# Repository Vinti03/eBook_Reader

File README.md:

# OpenBook E-Book Reader
Made by: Vintilescu Andrei-Florin, 332CA

University: UNSTPB, Bucharest

## Conținutul Repository-ului

OpenBook

    Hardware

        OpenBook.sch            // Fișierul schematic

        OpenBook.brd            // Fișierul PCB

    Manufacturing

        gerbers.zip             // Pachetul Gerber generat

        OpenBook.bom            // Bill Of Materials (BOM)

        OpenBook.cpl            // Fișier Pick and Place

    Mechanical

        OpenBook_exploded.step  // Model 3D exploded view (PCB + baterie + display + carcasă)

        OpenBook_Fusion360.f3d  // Fișierul 3D nativ Fusion360

    Images

        pcb_render.png          // Imagine cu randări ale PCB-ului

        device_render.png       // Randări ale dispozitivului complet

    LICENSE                     // Licența open source (ex. Apache 2.0)

    README.md                   // Acest fișier

## Diagramă Bloc a Sistemului

## Bill Of Materials (BOM)

| Device                                                                                  | DATASHEET                                                                                                     | PURCHASE-URL                                                                                                                            |
|-----------------------------------------------------------------------------------------|---------------------------------------------------------------------------------------------------------------|-----------------------------------------------------------------------------------------------------------------------------------------|
| ADAFRUIT_LEDCHIP-LED0603                                                                | https://www.snapeda.com/parts/KP-1608SURCK/Kingbright/datasheet/                                              | https://www.snapeda.com/parts/KP-1608SURCK/Kingbright/view-part/?ref=search&t=LED%200603                                                  |
| ESP32_WROVER_EAGLE-LTSPICE_RR0402                                                       | https://analytics.supplyframe.com/trackingservlet/track/?r=0x34... (link lung)                                | https://componentsearchengine.com/part-view/R0402%201%25%20100%20K%20(RC0402FR-07100KL)/YAGEO                                          |
| SJ                                                                                      | https://grabcad.com/library/solder-jumpers-1                                                                  | https://grabcad.com/library/solder-jumpers-1                                                                                            |
| EAGLE-LTSPICE_CC0402                                                                    | https://analytics.supplyframe.com/trackingservlet/track/?r=0x34... (link lung)                                | https://componentsearchengine.com/part-view/CC0402MRX5R5BB106/YAGEO                                                                    |
| ESP32_WROVER_EAGLE-LTSPICE_RR0402                                                       | https://analytics.supplyframe.com/trackingservlet/track/?r=0x34... (link lung)                                | https://componentsearchengine.com/part-view/R0402%201%25%20100%20K%20(RC0402FR-07100KL)/YAGEO                                          |
| ESP32_WROVER_EAGLE-LTSPICE_RR0402                                                       | https://analytics.supplyframe.com/trackingservlet/track/?r=0x34... (link lung)                                | https://componentsearchengine.com/part-view/R0402%201%25%20100%20K%20(RC0402FR-07100KL)/YAGEO                                          |
| EAGLE-LTSPICE_CC0402                                                                    | https://analytics.supplyframe.com/trackingservlet/track/?r=0x34... (link lung)                                | https://componentsearchengine.com/part-view/CC0402MRX5R5BB106/YAGEO                                                                    |
| RCL_CPOL-EUCT3528                                                                       | https://s3.amazonaws.com/snapeda/datasheet/TAJB475K025RNJ_AVX.pdf                                             | https://www.snapeda.com/parts/TAJB475K025RNJ/AVX/view-part/?ref=dk&t=capacitor%203528&con_ref=None                                     |
| ESP32_WROVER_EAGLE-LTSPICE_RR0402                                                       | https://analytics.supplyframe.com/trackingservlet/track/?r=0x34... (link lung)                                | https://componentsearchengine.com/part-view/R0402%201%25%20100%20K%20(RC0402FR-07100KL)/YAGEO                                          |
| ESP32_WROVER_EAGLE-LTSPICE_RR0402                                                       | https://analytics.supplyframe.com/trackingservlet/track/?r=0x34... (link lung)                                | https://componentsearchengine.com/part-view/R0402%201%25%20100%20K%20(RC0402FR-07100KL)/YAGEO                                          |
| EAGLE-LTSPICE_CC0402                                                                    | https://analytics.supplyframe.com/trackingservlet/track/?r=0x34... (link lung)                                | https://componentsearchengine.com/part-view/CC0402MRX5R5BB106/YAGEO                                                                    |
| 112A-TAAR-R03_ATTEND                                                                    | https://store.comet.srl.ro/Catalogue/Product/43497/                                                           | https://store.comet.srl.ro/Catalogue/Product/43497/                                                                                     |
| ESP32_WROVER_EAGLE-LTSPICE_RR0402                                                       | https://analytics.supplyframe.com/trackingservlet/track/?r=0x34... (link lung)                                | https://componentsearchengine.com/part-view/R0402%201%25%20100%20K%20(RC0402FR-07100KL)/YAGEO                                          |
| EAGLE-LTSPICE_CC0402                                                                    | https://analytics.supplyframe.com/trackingservlet/track/?r=0x34... (link lung)                                | https://componentsearchengine.com/part-view/CC0402MRX5R5BB106/YAGEO                                                                    |
| EAGLE-LTSPICE_CC0402                                                                    | https://analytics.supplyframe.com/trackingservlet/track/?r=0x34... (link lung)                                | https://componentsearchengine.com/part-view/CC0402MRX5R5BB106/YAGEO                                                                    |
| ESP32_WROVER_EAGLE-LTSPICE_RR0402                                                       | https://analytics.supplyframe.com/trackingservlet/track/?r=0x34... (link lung)                                | https://componentsearchengine.com/part-view/R0402%201%25%20100%20K%20(RC0402FR-07100KL)/YAGEO                                          |
| ESP32_WROVER_EAGLE-LTSPICE_RR0402                                                       | https://analytics.supplyframe.com/trackingservlet/track/?r=0x34... (link lung)                                | https://componentsearchengine.com/part-view/R0402%201%25%20100%20K%20(RC0402FR-07100KL)/YAGEO                                          |
| ESP32_WROVER_SPARKFUN-DISCRETESEMI_MOSFET_PCH-DMG2305UX-7                               | https://analytics.supplyframe.com/trackingservlet/track/?r=0x34... (link lung)                                | https://componentsearchengine.com/part-view/DMG2305UX-7/Diodes%20Incorporated                                                         |
| ESP32_WROVER_EAGLE-LTSPICE_RR0402                                                       | https://analytics.supplyframe.com/trackingservlet/track/?r=0x34... (link lung)                                | https://componentsearchengine.com/part-view/R0402%201%25%20100%20K%20(RC0402FR-07100KL)/YAGEO                                          |
| EAGLE-LTSPICE_CC0402                                                                    | https://analytics.supplyframe.com/trackingservlet/track/?r=0x34... (link lung)                                | https://componentsearchengine.com/part-view/CC0402MRX5R5BB106/YAGEO                                                                    |
| EAGLE-LTSPICE_CC0402                                                                    | https://analytics.supplyframe.com/trackingservlet/track/?r=0x34... (link lung)                                | https://componentsearchengine.com/part-view/CC0402MRX5R5BB106/YAGEO                                                                    |
| ESP32_WROVER_EAGLE-LTSPICE_RR0402                                                       | https://analytics.supplyframe.com/trackingservlet/track/?r=0x34... (link lung)                                | https://componentsearchengine.com/part-view/R0402%201%25%20100%20K%20(RC0402FR-07100KL)/YAGEO                                          |
| 744043680IND_4828-WE-TPC_WRE                                                             | https://www.we-online.com/components/products/datasheet/744043680.pdf                                        | https://eu.mouser.com/ProductDetail/Wurth-Elektronik/744043680?qs=PGXP4M47uW6VkZq%252BkzjrHA%3D%3D                                      |
| BD5229G-TR                                                                              | https://analytics.supplyframe.com/trackingservlet/track/?r=0x34... (link lung)                                | https://componentsearchengine.com/part-view/XC6220A331MR-G/Torex                                                                       |
| ESP32_WROVER_BME680_BME680                                                              | https://www.snapeda.com/parts/BME680/Bosch%20Sensortec/datasheet/                                             | https://www.google.com/url?q=https://www.snapeda.com/parts/BME680/Bosch/view-part/?welcome%3Dhome&sa=D&source=editors&ust=...&usg=... |
| BUTTON_CUSYOMV1                                                                         | https://industry.panasonic.com/global/en/downloads?tab=catalog&small_g_cd=203&part_no=EVQPUJ02K             | https://industry.panasonic.com/global/en/products/control/switch/light-touch/number/evqpuj02k                                           |
| CPH3225A                                                                                | https://www.snapeda.com/parts/CPH3225A/Seiko%20Instruments/datasheet/                                         | https://www.snapeda.com/parts/CPH3225A/Seiko+Instruments/view-part/?ref=eda                                                             |
| DS3231SN#                                                                               | https://www.snapeda.com/parts/DS3231SN%23/Analog%20Devices/datasheet/                                         | https://www.snapeda.com/parts/DS3231SN%23/Analog+Devices/view-part/?ref=eda                                                             |
| ESP32-C6-WROOM-1-N8                                                                     | https://www.snapeda.com/parts/ESP32-C6-WROOM-1-N8/Espressif%20Systems/datasheet/                              | https://www.snapeda.com/parts/ESP32-C6-WROOM-1-N8/Espressif+Systems/view-part/?ref=eda                                                  |
| ESP32C6_VARISTORCN1812                                                                  | https://www.snapeda.com/parts/MOV-10D561K/Bourns/datasheet/                                                   | https://www.snapeda.com/parts/MOV-10D561K/Bourns/view-part/?welcome=home&ref=search&t=varistor                                           |
| ESP32_WROVER_AVX---SD0805S020S1R0_AVX_SD0805S020S1R0_0_0AVX_SD0805S020S1R0_0_0          | https://ro.mouser.com/datasheet/2/40/schottky-3165252.pdf                                                     | https://ro.mouser.com/ProductDetail/KYOCERA-AVX/SD0805S020S1R0?qs=jCA%252BPfw4LHbpkAoSnwrdjw%3D%3D                                      |
| ESP32_WROVER_SPARKFUN-IC-POWER_MCP73831                                                 | https://eu.mouser.com/datasheet/2/268/MCP73831_Family_Data_Sheet_DS20001984H-3441711.pdf                      | https://eu.mouser.com/ProductDetail/Microchip-Technology/MCP73831T-2ACI-OT?qs=yUQqVecv4qvbBQBGbHx0Mw%3D%3D                              |
| FH34SRJ-24S-0.5SH_99_                                                                   | https://analytics.supplyframe.com/trackingservlet/track/?r=0x34... (link lung)                                | https://componentsearchengine.com/part-view/FH34SRJ-24S-0.5SH(99)/Hirose                                                               |
| MAX17048G+T10                                                                           | https://www.snapeda.com/parts/MAX17048G+T10/Analog%20Devices/datasheet/                                       | https://www.snapeda.com/parts/MAX17048G+T10/Analog+Devices/view-part/?ref=eda                                                           |
| MBR0530                                                                                 | https://www.snapeda.com/parts/MBR0530/ON%20Semiconductor/datasheet/                                           | https://www.snapeda.com/parts/MBR0530/Onsemi/view-part/?ref=eda                                                                         |
| PGB1010603MR                                                                            | https://www.snapeda.com/parts/PGB1010603MR/Littelfuse%20Inc./datasheet/                                       | https://www.snapeda.com/parts/PGB1010603MR/Littelfuse/view-part/?ref=eda                                                                |
| QWIIC_RIGHT_ANGLE                                                                       | https://eu.mouser.com/ProductDetail/Adafruit/4208?qs=PzGy0jfpSMtbScLbr0L5dw%3D%3D                           | https://eu.mouser.com/ProductDetail/Adafruit/4208?qs=PzGy0jfpSMtbScLbr0L5dw%3D%3D                                                     |
| SAMACSYS_PARTS_USB4110-GF-A                                                             | https://analytics.supplyframe.com/trackingservlet/track/?r=0x34... (link lung)                                | https://componentsearchengine.com/part-view/USB4110-GF-A/GCT%20(GLOBAL%20CONNECTOR%20TECHNOLOGY)                                        |
| ESP32_WROVER_AVX---SD0805S020S1R0_AVX_SD0805S020S1R0_0_0AVX_SD0805S020S1R0_0_0          | https://ro.mouser.com/datasheet/2/40/schottky-3165252.pdf                                                     | https://ro.mouser.com/ProductDetail/KYOCERA-AVX/SD0805S020S1R0?qs=jCA%252BPfw4LHbpkAoSnwrdjw%3D%3D                                      |
| SI1308EDL-T1-GE3                                                                        | https://www.snapeda.com/parts/SI1308EDL-T1-GE3/Vishay%20Siliconix/datasheet/                                   | https://www.snapeda.com/parts/SI1308EDL-T1-GE3/Vishay+Siliconix/view-part/?ref=eda                                                      |
| TPTP20R                                                                                 | self made                                                                                                     | self made                                                                                                                               |
| USBLC6-2SC6Y                                                                            | https://www.snapeda.com/parts/USBLC6-2SC6Y/STMicroelectronics/datasheet/                                      | https://www.snapeda.com/parts/USBLC6-2SC6Y/STMicroelectronics/view-part/?ref=eda                                                        |
| W25Q512JVEIQ                                                                            | https://www.snapeda.com/parts/W25Q512JVEIQ/Winbond%20Electronics/datasheet/                                   | https://www.snapeda.com/parts/W25Q512JVEIQ/Winbond+Electronics/view-part/?ref=eda                                                       |
| XC6220A331MR-G                                                                          | https://analytics.supplyframe.com/trackingservlet/track/?r=0x34... (link lung)                                |                                                                                                                                         |

*Notă:* De asemenea lista completa de componente cu linkurile complete pentru datasheet si purchase-url o gasiti consultand fișierul `BOM.csv` inclus în directorul Manufacturing.

---

## Funcționalitatea Hardware în Detaliu

Acest proiect integrează următoarele module și componente:

- **ESP32-C6 Microcontroller:**  
  - Rol: Procesare centrală și interfațare cu toate componentele.  
  - Interfețe:  
    - UART pentru comunicare cu modulul e-Paper  
    - SPI pentru senzorii periferici  
    - I2C pentru conectarea accelerometrului și a altor senzori  
  - Specificații: Calcul estimativ de consum energetic, rutare optimizată a pinilor și implementare a planurilor de masă pe ambele straturi (TOP și BOTTOM) pentru stabilitate electrică.

- **Display e-Paper:**  
  - Rol: Afișare de text și imagini cu consum redus de energie.  
  - Interfață: SPI, cu un set dedicat de pini conectați direct la ESP32-C6.
  
- **Baterie LiPo:**  
  - Rol: Alimentarea dispozitivului.  
  - Observații: Bateria este conectată direct la patru test pad-uri conform specificațiilor pentru economisirea spațiului.  
 
- **Decuplaje și Protecții:**  
  - Utilizare condensatoare 100 nF amplasate cât mai aproape de pinii de alimentare pentru a asigura o decuplare corespunzătoare.  
  - Rutare a traseelor de putere la 0.3mm, iar semnalele de date la cel puțin 0.15mm conform specificațiilor.

- **Plan de Masă și Rutare:**  
  - Implementare a unui plan de masă atât pe layer-ul TOP cât și pe BOTTOM.  
  - Vias-urile au fost plasate strategic și folosim tehnici de Via Stitching, în special în zona modulului ESP32, pentru a minimiza interferențele.

- **Constrângeri Mecanice:**  
  - PCB-ul de 1mm grosime este proiectat să se încadreze perfect în carcasa specificată.  
  - Toate componentele principale sunt grupate în jurul microcontroller-ului și amplasate exclusiv pe layer-ul TOP de conformitate cu cerințele proiectului.

---

## Configurarea și Utilizarea Pinii ESP32-C6

Mai jos este un sumar al pinilor utilizați și a motivelor alese:

| Pin ESP32-C6 | Funcționalitate Asociată         | Motiv/Observații                              |
|--------------|----------------------------------|-----------------------------------------------|
| GPIO12       | SPI_MISO pentru Display e-Paper  | Necesită viteză mare și stabilitate la semnal  |
| GPIO13       | SPI_MOSI pentru Display e-Paper  | Pentru comunicații rapide și fiabile           |
| GPIO14       | SPI_CLK pentru Display e-Paper   | Sincronizare precisă a semnalului              |
| GPIO15       | CS (Chip Select) pentru e-Paper  | Control dedicated pentru selecție modul         |
| GPIO2        | I2C SDA pentru Senzori           | Interfață I2C standard pentru accelerometru/senzori |
| GPIO4        | I2C SCL pentru Senzori           | Necesită semnal clar pentru sincronizarea I2C  |
| ...          | Alte pini alocați conform necesităților proiectului | Consultare schema detaliată pentru alocare        |

## Concluzie

  Proiectul OpenBook a urmarit dezvoltarea unui dispozitiv e-book reader accesibil, open-source, cu un design hardware optimizat pentru productie de masa. Am parcurs toate etapele de validare, de la schema electrica si PCB pana la integrarea mecanica completa in carcasa finala. Design-ul respecta constrangerile functionale, mecanice si de buna practica, fiind pregatit pentru testare si productie. Documentatia completa si fisierele necesare sunt disponibile in acest repository.

---

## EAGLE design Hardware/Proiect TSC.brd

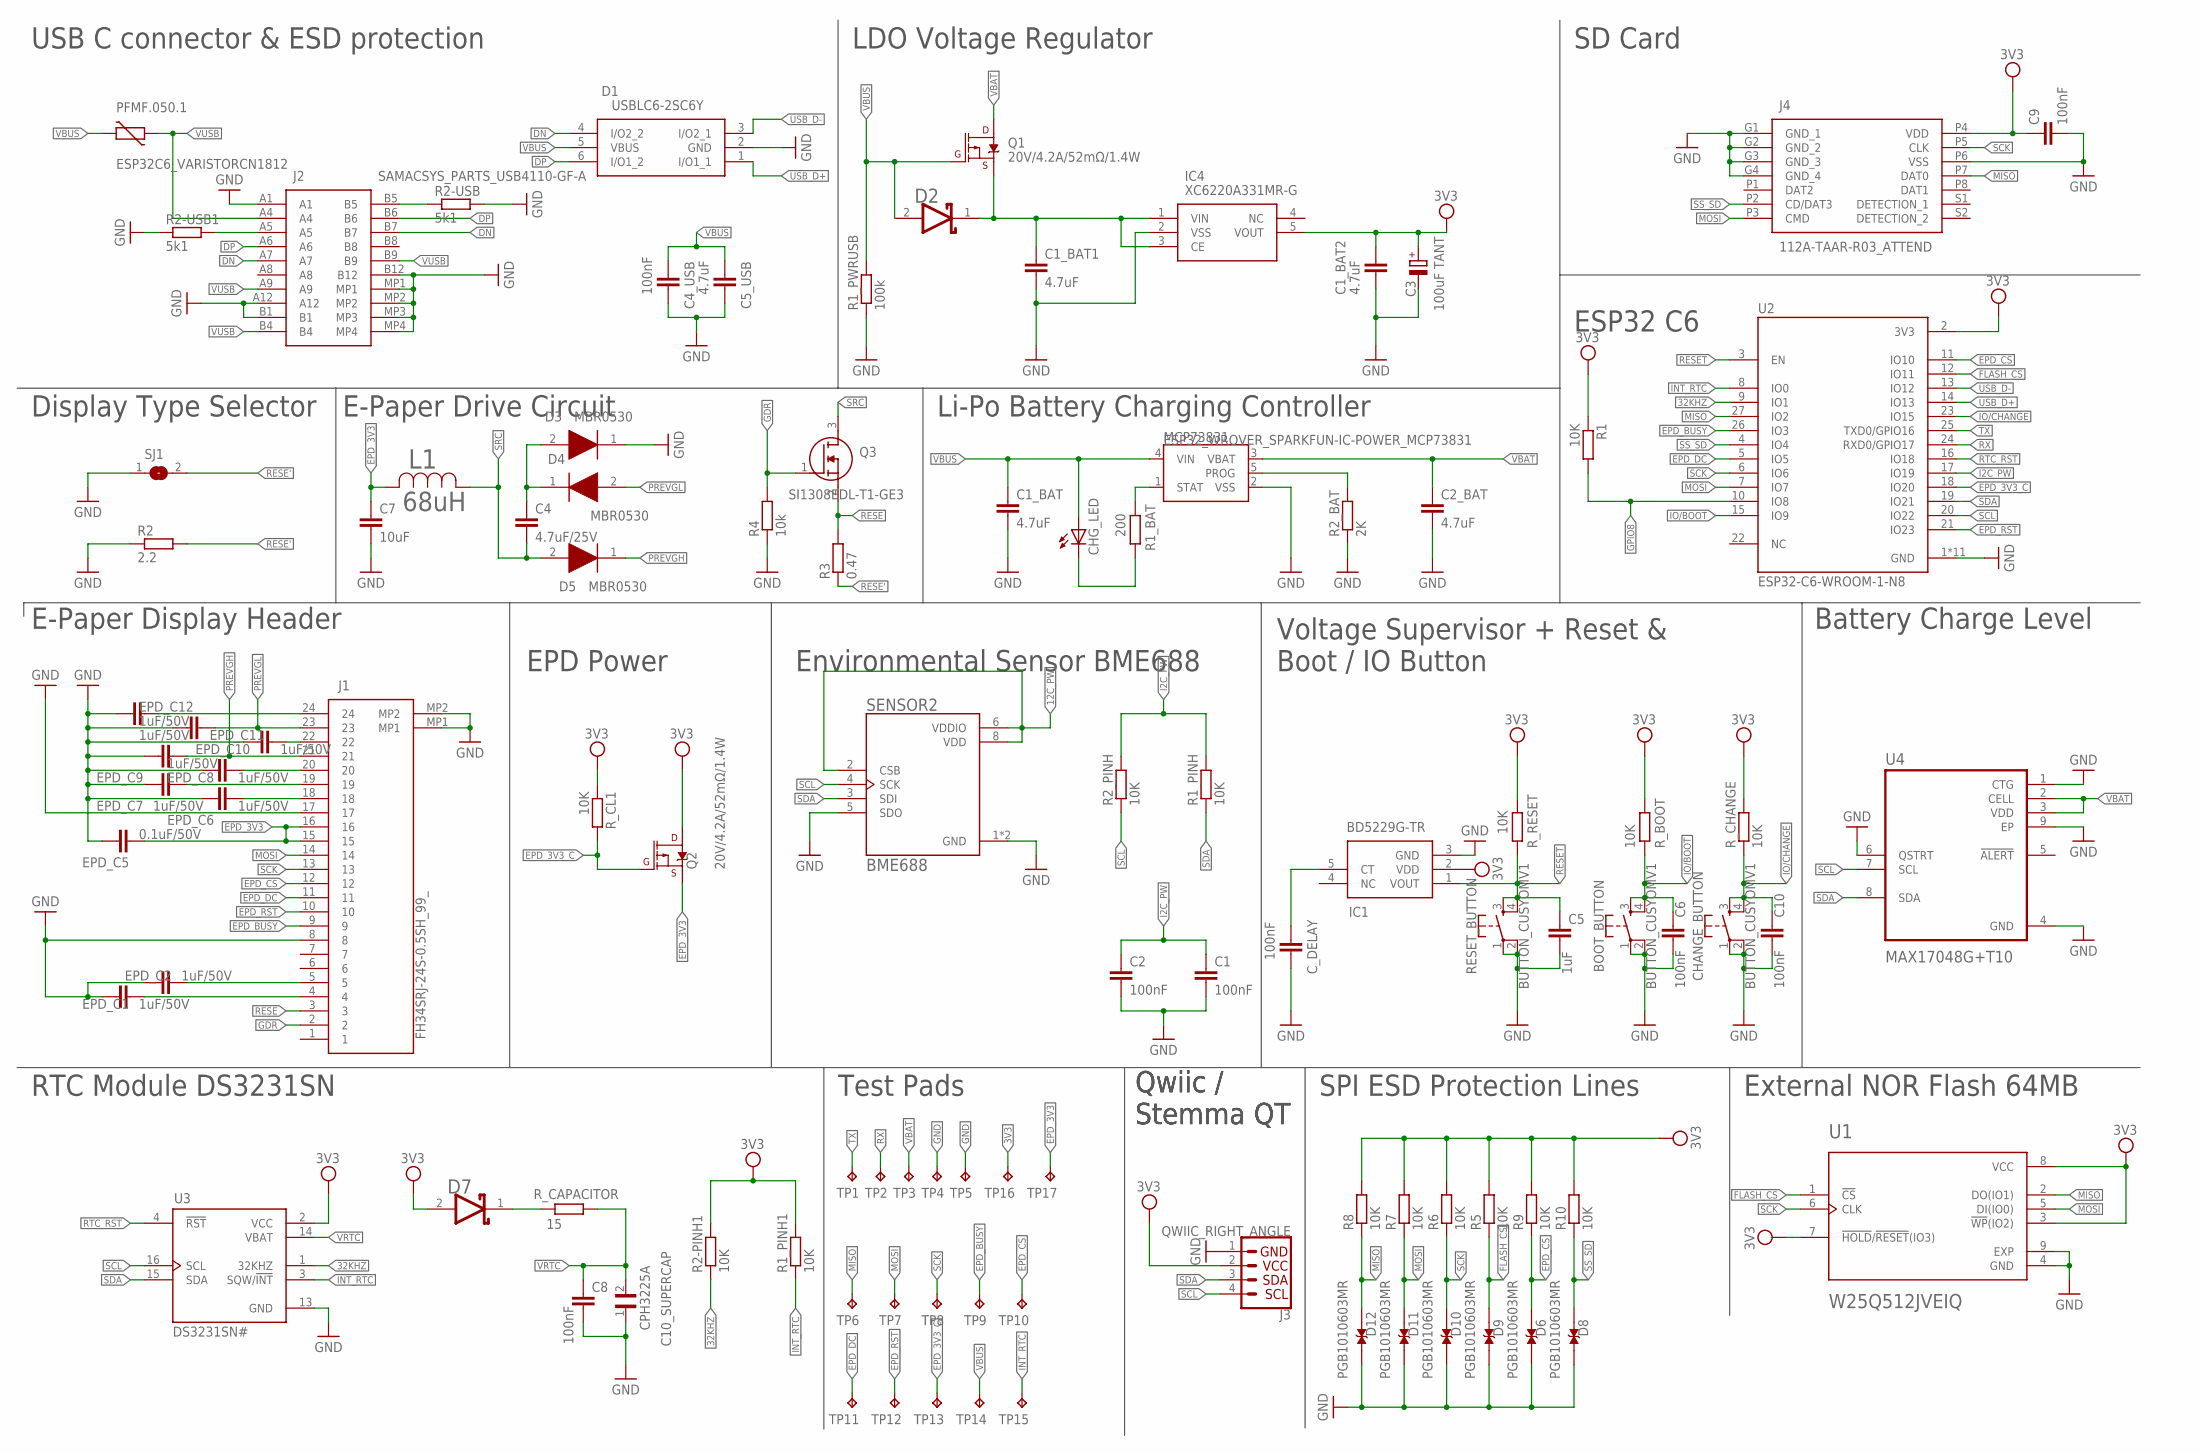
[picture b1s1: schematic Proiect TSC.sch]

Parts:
BOOT_BUTTON: BUTTON_CUSYOMV1; MYBUTTON
C1, C2, C4_USB, C6, C8, C9, C10: 100nF; EAGLE-LTSPICE_C0402
C1_BAT, C1_BAT1, C1_BAT2, C2_BAT, C5_USB: 4.7uF; EAGLE-LTSPICE_C0402
C3: 100uF TANT; RCL_CT3528
C4: 4.7uF/25V; EAGLE-LTSPICE_C0402
C5: 1uF; EAGLE-LTSPICE_C0402
C7: 10uF; EAGLE-LTSPICE_C0402
C10_SUPERCAP: CPH3225A; CAPCP3225X100N
CHANGE_BUTTON: BUTTON_CUSYOMV1; MYBUTTON
CHG_LED: ADAFRUIT_LEDCHIP-LED0603; ADAFRUIT_CHIP-LED0603
C_DELAY: 100nF; EAGLE-LTSPICE_C0402
D1: USBLC6-2SC6Y; SOT95P280X145-6N
D2: SD0805S020S1R0; ESP32_WROVER_AVX---SD0805S020S1R0_AVX_SD0805S020S1R0_0
D3, D4, D5: MBR0530; SOD3716X135N
D6, D8, D9, D10, D11, D12: PGB1010603MR; DIOC1608X36N
D7: ESP32_WROVER_AVX---SD0805S020S1R0_AVX_SD0805S020S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; ESP32_WROVER_AVX---SD0805S020S1R0_AVX_SD0805S020S1R0_0
EPD_C1, EPD_C2, EPD_C6, EPD_C7, EPD_C8, EPD_C9, EPD_C10, EPD_C11, EPD_C12: 1uF/50V; EAGLE-LTSPICE_C0402
EPD_C5: 0.1uF/50V; EAGLE-LTSPICE_C0402
IC1: BD5229G-TR; SOT95P280X120-5N
IC4: XC6220A331MR-G; SOT95P280X120-5N
J1: FH34SRJ-24S-0.5SH_99_; FH34SRJ24S05SH99
J2: SAMACSYS_PARTS_USB4110-GF-A; SAMACSYS_PARTS_USB4110GFA
J3: QWIIC_RIGHT_ANGLE; JST04_1MM_RA
J4: 112A-TAAR-R03_ATTEND; 112ATAARR03ATTEND
L1: 68uH; IND_4828-WE-TPC_WRE
MCP73831: ESP32_WROVER_SPARKFUN-IC-POWER_MCP73831; ESP32_WROVER_SPARKFUN-IC-POWER_SOT23-5
PFMF.050.1: ESP32C6_VARISTORCN1812; ESP32C6_VARISTOR_CT/CN1812
Q1, Q2: 20V/4.2A/52mΩ/1.4W; ESP32_WROVER_SPARKFUN-DISCRETESEMI_SOT23-3
Q3: SI1308EDL-T1-GE3; SOT65P210X110-3N
R1, R1_PINH, R1_PINH1, R2-PINH1, R2_PINH, R5, R6, R7, R8, R9, R10: 10K; ESP32_WROVER_EAGLE-LTSPICE_R0402
R1_BAT: 200; ESP32_WROVER_EAGLE-LTSPICE_R0402
R1_PWRUSB: 100k; ESP32_WROVER_EAGLE-LTSPICE_R0402
R2: 2.2; ESP32_WROVER_EAGLE-LTSPICE_R0402
R2-USB, R2-USB1: 5k1; ESP32_WROVER_EAGLE-LTSPICE_R0402
R2_BAT: 2K; ESP32_WROVER_EAGLE-LTSPICE_R0402
R3: 0.47; ESP32_WROVER_EAGLE-LTSPICE_R0402
R4: 10k; ESP32_WROVER_EAGLE-LTSPICE_R0402
RESET_BUTTON: BUTTON_CUSYOMV1; MYBUTTON
R_BOOT: 10K; ESP32_WROVER_EAGLE-LTSPICE_R0402
R_CAPACITOR: 15; ESP32_WROVER_EAGLE-LTSPICE_R0402
R_CHANGE: 10K; ESP32_WROVER_EAGLE-LTSPICE_R0402
R_CL1: 10K; ESP32_WROVER_EAGLE-LTSPICE_R0402
R_RESET: 10K; ESP32_WROVER_EAGLE-LTSPICE_R0402
SENSOR2: BME688; ESP32_WROVER_BME680_PSON80P300X300X100-8N
SJ1: SJ
TP1, TP2, TP3, TP4, TP5, TP6, TP7, TP8, TP9, TP10, TP11, TP12, TP13, TP14, TP15, TP16, TP17: TPTP20R; TP20R
U1: W25Q512JVEIQ; SON127P600X800X80-9N
U2: ESP32-C6-WROOM-1-N8; XCVR_ESP32-C6-WROOM-1-N8
U3: DS3231SN#; SOIC127P1032X265-16N
U4: MAX17048G+T10; SON50P200X200X80-9N

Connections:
3V3: C1_BAT2.1, C3.+, C9.1, D7.2 (ANODE), IC1.2 (VDD), IC4.5 (VOUT), J3.2, J4.P4 (VDD), Q2.3 (D), R1.1, R1_PINH1.2, R2-PINH1.2, R5.2, R6.2, R7.2, R8.2, R9.2, R10.2, R_BOOT.2, R_CHANGE.2, R_CL1.1, R_RESET.2, TP16.TP, U1.3 (!WP!(IO2)), U1.7 (!HOLD!/!RESET!(IO3)), U1.8 (VCC), U2.2 (3V3), U3.2 (VCC)
12C_PW: SENSOR2.2 (CSB), SENSOR2.6 (VDDIO), SENSOR2.8 (VDD)
32KHZ: R2-PINH1.1, U2.9 (IO1), U3.1 (32KHZ)
DN: D1.4 (I/O2_2), J2.A7, J2.B7
DP: D1.6 (I/O1_2), J2.A6, J2.B6
EPD_3V3: C7.1, EPD_C5.1, J1.15, J1.16, L1.2, Q2.2 (S), TP17.TP
EPD_3V3_C: Q2.1 (G), R_CL1.2, TP13.TP, U2.18 (IO20)
EPD_BUSY: J1.9, TP9.TP, U2.26 (IO3)
EPD_CS: D6.2, J1.12, R9.1, TP10.TP, U2.11 (IO10)
EPD_DC: J1.11, TP11.TP, U2.5 (IO5)
EPD_RST: J1.10, TP12.TP, U2.21 (IO23)
FLASH_CS: D9.2, R5.1, U1.1 (!CS), U2.12 (IO11)
GDR: J1.2, Q3.1 (G), R4.2
GND: BOOT_BUTTON.1, BOOT_BUTTON.2, C1.2, C1_BAT.2, C1_BAT1.2, C1_BAT2.2, C2.2, C2_BAT.2, C3.-, C4_USB.2, C5.2, C5_USB.2, C6.2, C7.2, C8.2, C9.2, C10.2, C10_SUPERCAP.1, CHANGE_BUTTON.1, CHANGE_BUTTON.2, C_DELAY.2, D1.2 (GND), D3.1 (K), D6.1, D8.1, D9.1, D10.1, D11.1, D12.1, EPD_C1.2, EPD_C2.2, EPD_C5.2, EPD_C6.2, EPD_C7.2, EPD_C8.2, EPD_C9.2, EPD_C10.2, EPD_C11.2, EPD_C12.2, IC1.3 (GND), IC4.2 (VSS), J1.8, J1.17, J1.MP1, J1.MP2, J2.A1, J2.A12, J2.B1, J2.B12, J2.MP1, J2.MP2, J2.MP3, J2.MP4, J3.1, J4.G1 (GND_1), J4.G2 (GND_2), J4.G3 (GND_3), J4.G4 (GND_4), J4.P6 (VSS), MCP73831.2 (VSS), R1_PWRUSB.1, R2.1, R2-USB.2, R2-USB1.1, R2_BAT.1, R4.1, RESET_BUTTON.1, RESET_BUTTON.2, SENSOR2.1 (GND), SENSOR2.5 (SDO), SENSOR2.7 (GND), SJ1.1, TP4.TP, TP5.TP, U1.4 (GND), U1.9 (EXP), U2.1 (GND), U2.28 (GND), U2.29_1 (GND), U2.29_2 (GND), U2.29_3 (GND), U2.29_4 (GND), U2.29_5 (GND), U2.29_6 (GND), U2.29_7 (GND), U2.29_8 (GND), U2.29_9 (GND), U3.13 (GND), U4.1 (CTG), U4.4 (GND), U4.6 (QSTRT), U4.9 (EP)
GPIO8: R1.2, U2.10 (IO8)
I2C_PW: C1.1, C2.1, R1_PINH.2, R2_PINH.2, U2.17 (IO19)
INT_RTC: R1_PINH1.1, TP15.TP, U2.8 (IO0), U3.3 (SQW/!INT)
IO/BOOT: BOOT_BUTTON.3, BOOT_BUTTON.4, C6.1, R_BOOT.1, U2.15 (IO9)
IO/CHANGE: C10.1, CHANGE_BUTTON.3, CHANGE_BUTTON.4, R_CHANGE.1, U2.23 (IO15)
MISO: D12.2, J4.P7 (DAT0), R8.1, TP6.TP, U1.2 (DO(IO1)), U2.27 (IO2)
MOSI: D11.2, J1.14, J4.P3 (CMD), R7.1, TP7.TP, U1.5 (DI(IO0)), U2.7 (IO7)
unnamed: CHG_LED.C, R1_BAT.1
unnamed: J2.A5, R2-USB1.2
unnamed: EPD_C12.1, J1.24
unnamed: C1_BAT1.1, D2.1 (CATHODE), IC4.1 (VIN), IC4.3 (CE), Q1.2 (S)
unnamed: C4.1, D3.2 (A), D4.1 (K)
unnamed: MCP73831.1 (STAT), R1_BAT.2
unnamed: MCP73831.5 (PROG), R2_BAT.2
unnamed: C_DELAY.1, IC1.5 (CT)
unnamed: EPD_C10.1, J1.22
unnamed: J2.B5, R2-USB.1
unnamed: D7.1 (CATHODE), R_CAPACITOR.2
unnamed: EPD_C8.1, J1.20
unnamed: EPD_C7.1, J1.19
unnamed: EPD_C6.1, J1.18
unnamed: EPD_C2.1, J1.5
unnamed: EPD_C1.1, J1.4
PREVGH: D5.1 (K), EPD_C9.1, J1.21
PREVGL: D4.2 (A), EPD_C11.1, J1.23
RESE: J1.3, Q3.2 (S), R3.2
RESE': R2.2, R3.1, SJ1.2
RESET: C5.1, IC1.1 (VOUT), RESET_BUTTON.3, RESET_BUTTON.4, R_RESET.1, U2.3 (EN)
RTC_RST: U2.16 (IO18), U3.4 (!RST)
RX: TP2.TP, U2.24 (RXD0/GPIO17)
SCK: D10.2, J1.13, J4.P5 (CLK), R6.1, TP8.TP, U1.6 (CLK), U2.6 (IO6)
SCL: J3.4, R2_PINH.1, SENSOR2.4 (SCK), U2.20 (IO22), U3.16 (SCL), U4.7 (SCL)
SDA: J3.3, R1_PINH.1, SENSOR2.3 (SDI), U2.19 (IO21), U3.15 (SDA), U4.8 (SDA)
SRC: C4.2, D5.2 (A), L1.1, Q3.3 (D)
SS_SD: D8.2, J4.P2 (CD/DAT3), R10.1, U2.4 (IO4)
TX: TP1.TP, U2.25 (TXD0/GPIO16)
USB_D+: D1.1 (I/O1_1), U2.14 (IO13)
USB_D-: D1.3 (I/O2_1), U2.13 (IO12)
VBAT: C2_BAT.1, MCP73831.3 (VBAT), Q1.3 (D), TP3.TP, U4.2 (CELL), U4.3 (VDD)
VBUS: C1_BAT.1, C4_USB.1, C5_USB.1, CHG_LED.A, D1.5 (VBUS), D2.2 (ANODE), MCP73831.4 (VIN), PFMF.050.1.2, Q1.1 (G), R1_PWRUSB.2, TP14.TP
VRTC: C8.1, C10_SUPERCAP.2, R_CAPACITOR.1, U3.14 (VBAT)
VUSB: J2.A4, J2.A9, J2.B4, J2.B9, PFMF.050.1.1

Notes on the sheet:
USB C connector & ESD protection
LDO Voltage Regulator
SD Card
Display Type Selector
E-Paper Drive Circuit
Li-Po Battery Charging Controller
ESP32 C6
E-Paper Display Header
EPD Power
Environmental Sensor BME688
Voltage Supervisor + Reset & Boot / IO Button
Battery Charge Level
RTC Module DS3231SN
Test Pads
Qwiic / Stemma QT
SPI ESD Protection Lines
External NOR Flash 64MB

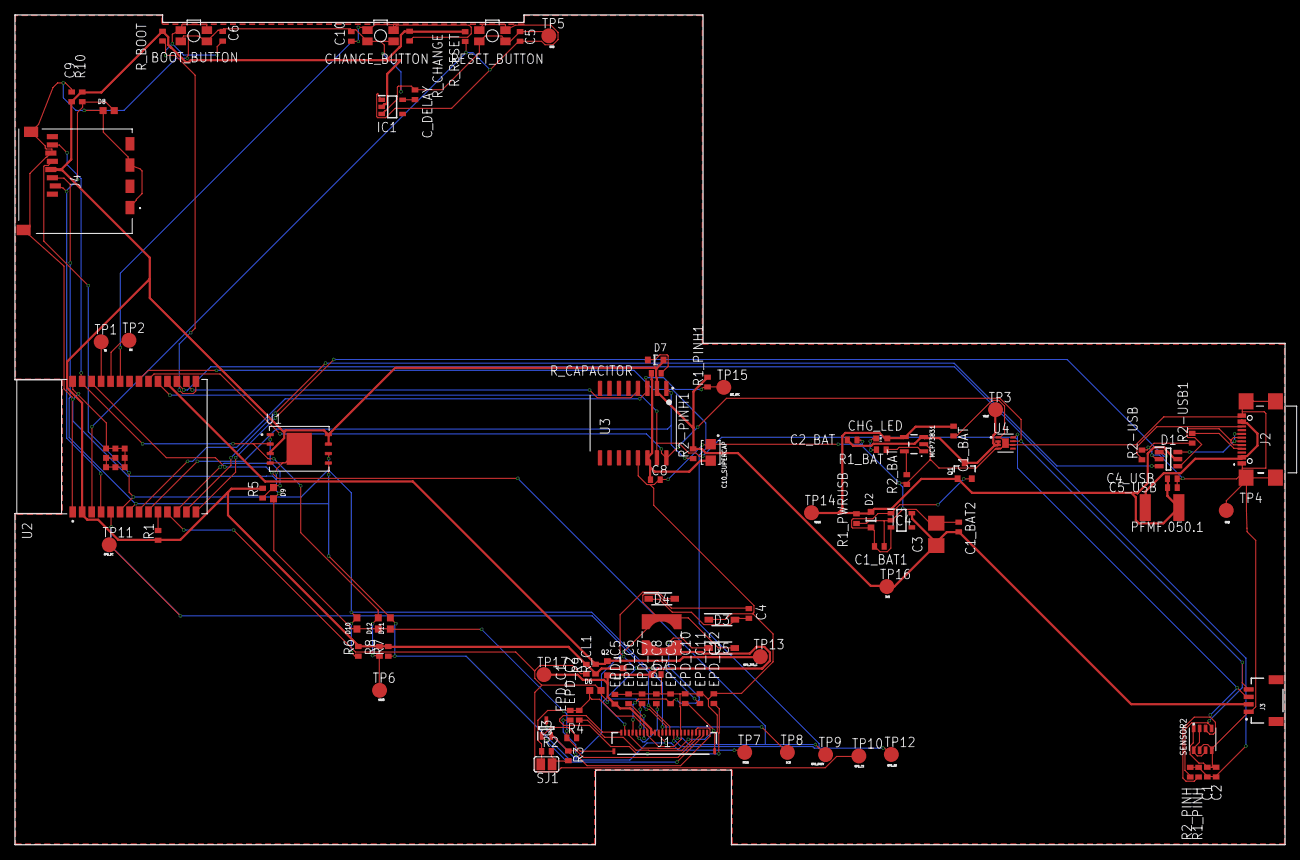
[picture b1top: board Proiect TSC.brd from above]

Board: 2 copper layers, 170.2 x 111.2 mm, 103 parts (0 on the bottom side), 56 nets.

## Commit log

2025-04-06 First commit to be safe than sorry :P
2025-04-06 Create LICENSE
2025-04-06 Hopefully, first full version...
2025-04-06 Readme updated
2025-04-06 Updated diagram
2025-04-13 Fixes #1 #2 #3 #4 #5 #6 #7 #8 #9

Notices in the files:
parts and their libraries:
COPYRIGHT: Copyright (C) 2024 Ultra Librarian. All rights reserved.
